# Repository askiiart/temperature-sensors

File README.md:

# Temperature Sensors

An nRF52840-based Zigbee temperature sensor for use with ESPHome, designed for efficiency

## Bill of Materials

|Name                        |Quantity needed|MOQ|Price |Quantity to order|Link                                                                                           |Total    |
|----------------------------|---------------|---|------|-----------------|-----------------------------------------------------------------------------------------------|---------|
|2450AT43F0100001E           |1              |1  |1.1034|1                |https://www.lcsc.com/product-detail/C17192881.html                                             |1.1034   |
|32.768k crystal             |1              |5  |0.2553|5                |https://www.lcsc.com/product-detail/C46257428.html                                             |1.2765   |
|32M crystal                 |1              |10 |0.0564|10               |https://www.lcsc.com/product-detail/C42464320.html                                             |0.564    |
|1pF cap                     |1              |100|0.0085|100              |https://www.lcsc.com/product-detail/C5137611.html                                              |0.85     |
|1.2pF cap                   |1              |100|0.0038|100              |https://www.lcsc.com/product-detail/C1638.html                                                 |0.38     |
|20pF cap                    |2              |100|0.0089|100              |https://www.lcsc.com/product-detail/C5137583.html                                              |0.89     |
|10uF cap                    |3              |50 |0.083 |50               |https://www.lcsc.com/product-detail/C1691.html                                                 |4.15     |
|1uF cap                     |1              |50 |0.0217|50               |https://www.lcsc.com/product-detail/C29936.html                                                |1.085    |
|100pF cap                   |2              |50 |0.0174|50               |https://www.lcsc.com/product-detail/C576846.html                                               |0.87     |
|47nF cap                    |1              |100|0.0077|100              |https://www.lcsc.com/product-detail/C576852.html                                               |0.77     |
|100nF cap                   |5              |50 |0.0179|50               |https://www.lcsc.com/product-detail/C5137636.html                                              |0.895    |
|100uF cap                   |1              |5  |0.3214|5                |https://www.lcsc.com/product-detail/C521072.html                                               |1.607    |
|1nF cap                     |1              |100|0.0049|100              |https://www.lcsc.com/product-detail/C17702741.html                                             |0.49     |
|10pF can                    |1              |100|0.0059|100              |https://www.lcsc.com/product-detail/C1634.html                                                 |0.59     |
|Green LED                   |1              |1  |0.29  |1                |https://www.digikey.com/en/products/detail/sunled/XZVG53W-8/4745971                            |0.29     |
|Red LED                     |1              |1  |0.27  |1                |https://www.digikey.com/en/products/detail/sunled/XZMDK53W-8/4745952                           |0.27     |
|Diodes                      |4              |50 |0.0112|50               |https://www.lcsc.com/product-detail/C191023.html                                               |0.56     |
|JST S3B-PH-SM4-TB           |2              |1  |0.57  |2                |https://www.digikey.com/en/products/detail/jst-sales-america-inc/S3B-PH-SM4-TB/926656          |1.14     |
|JST S2B-PH-SM4-TB           |1              |5  |0.2055|5                |https://www.lcsc.com/product-detail/C295747.html                                               |1.0275   |
|4.7nH inductor              |1              |5  |0.0863|5                |https://www.lcsc.com/product-detail/C2043858.html                                              |0.4315   |
|2.2nH inductor              |1              |10 |0.0785|10               |https://www.lcsc.com/product-detail/C412264.html                                               |0.785    |
|10uH inductor               |1              |10 |0.0564|10               |https://www.lcsc.com/product-detail/C76798.html                                                |0.564    |
|15nH inductor               |1              |20 |0.0666|20               |https://www.lcsc.com/product-detail/C98055.html                                                |1.332    |
|AO3401A (PMOS)              |3              |20 |0.0371|20               |https://www.lcsc.com/product-detail/C347476.html                                               |0.742    |
|1M resistor                 |3              |100|0.0037|100              |https://www.lcsc.com/product-detail/C2907003.html                                              |0.37     |
|10k resistor                |2              |100|0.0057|100              |https://www.lcsc.com/product-detail/C844918.html                                               |0.57     |
|5.1k resistor               |2              |100|0.0028|100              |https://www.lcsc.com/product-detail/C2907044.html                                              |0.28     |
|100k resistor               |1              |100|0.0025|100              |https://www.lcsc.com/product-detail/C2907088.html                                              |0.25     |
|300 resistor                |2              |100|0.0029|100              |https://www.lcsc.com/product-detail/C2930092.html                                              |0.29     |
|560k resistor               |1              |100|0.0025|100              |https://www.lcsc.com/product-detail/C23203.html                                                |0.25     |
|180k resistor               |1              |100|0.0027|100              |https://www.lcsc.com/product-detail/C2906999.html                                              |0.27     |
|TS-1088-AR02016 (pushbutton)|1              |10 |0.0557|10               |https://www.lcsc.com/product-detail/C720477.html                                               |0.557    |
|CHS-01B1 (slide switch)     |1              |1  |0.7583|1                |https://www.lcsc.com/product-detail/C3312309.html                                              |0.7583   |
|NTC themistor               |1              |10 |0.0597|10               |https://www.lcsc.com/product-detail/C3152998.html                                              |0.597    |
|nRF52840-QFAA-F-R7          |1              |1  |6.54  |1                |https://www.digikey.com/en/products/detail/nordic-semiconductor-asa/NRF52840-QFAA-F-R7/15929801|6.54     |
|TP4057                      |1              |10 |0.0413|10               |https://www.lcsc.com/product-detail/C725791.html                                               |0.413    |
|TPS63051RMWR                |1              |1  |1.022 |1                |https://www.lcsc.com/product-detail/C139412.html                                               |1.022    |
|SN74LVC1G00DCKR (inverter)  |1              |10 |0.0299|10               |https://www.lcsc.com/product-detail/C19829626.html                                             |0.299    |
|                            |               |   |      |                 |                                                                                               |         |
|PCB                         |1              |1  |2     |1                |https://cart.jlcpcb.com/quote                                                                  |2        |
|                            |               |   |      |                 |                                                                                               |         |
|JLCPCB shipping             |               |   |      |                 |                                                                                               |3.12     |
|LCSC shipping               |               |   |      |                 |                                                                                               |10.76    |
|Digikey shipping            |               |   |      |                 |                                                                                               |$4.99    |
|                            |               |   |      |                 |                                                                                               |         |
|Subtotal                    |               |   |      |                 |                                                                                               |55.9992  |
|Total                       |               |   |      |                 |                                                                                               |60.619134|

## Production notes

The layer stackup should be JLC0616H-3313.

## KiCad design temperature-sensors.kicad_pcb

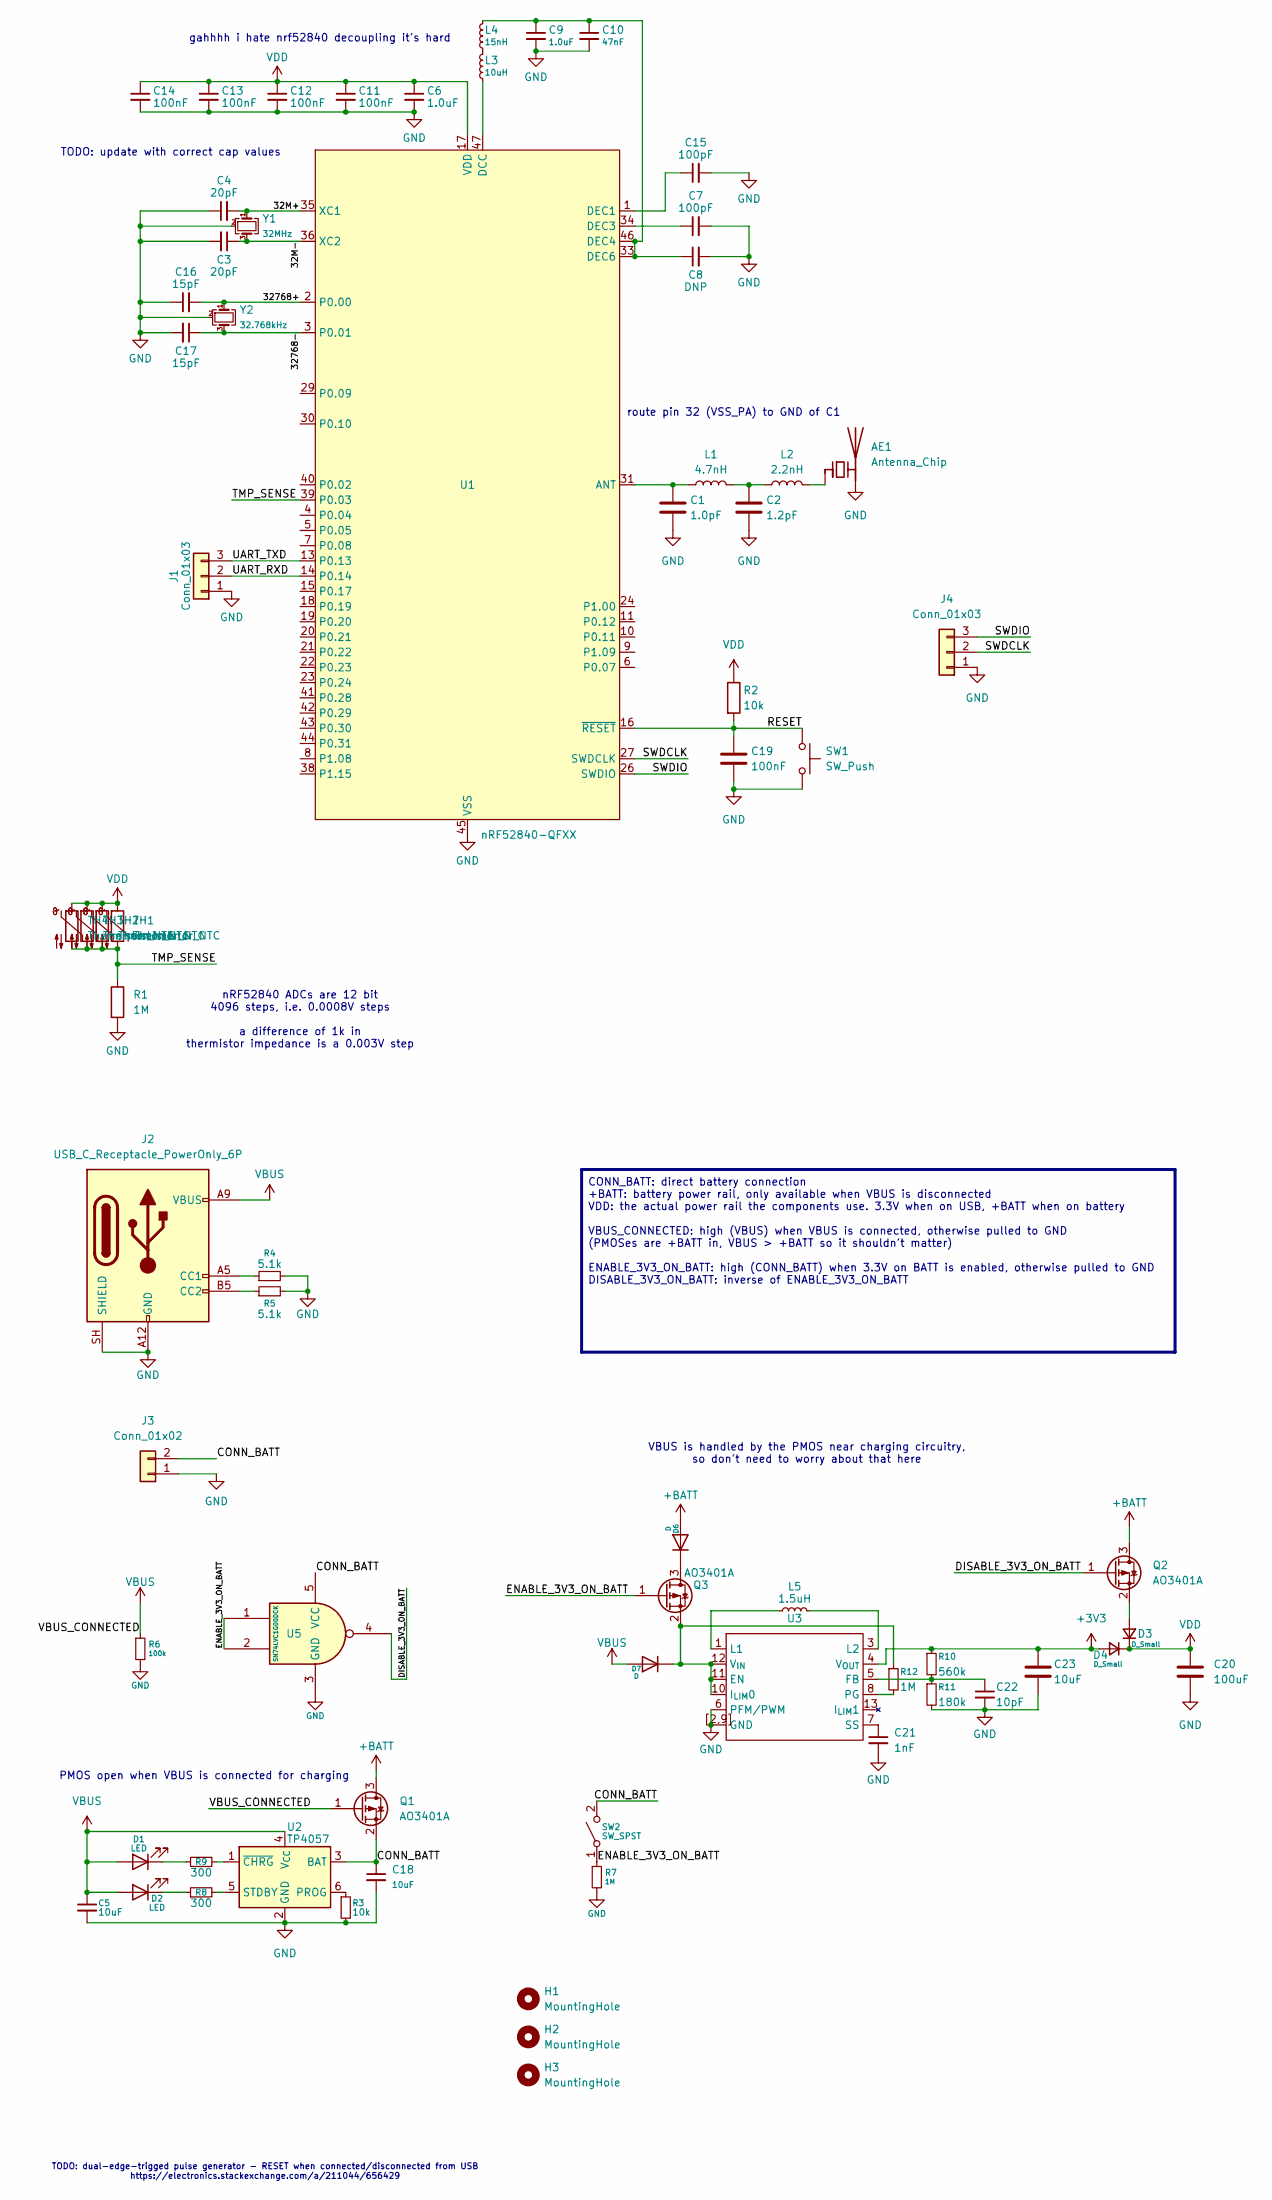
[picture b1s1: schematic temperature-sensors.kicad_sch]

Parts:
AE1: Antenna_Chip; Johanson_2450AT43F0100
C1: 1.0pF; C_0603_1608Metric
C2: 1.2pF; C_0603_1608Metric
C3, C4: 20pF; C_0603_1608Metric
C5, C18, C23: 10uF; C_0603_1608Metric
C6, C9: 1.0uF; C_0603_1608Metric
C7, C15: 100pF; C_0603_1608Metric
C8: DNP; C_0603_1608Metric
C10: 47nF; C_0603_1608Metric
C11, C12, C13, C14, C19: 100nF; C_0603_1608Metric
C16, C17: 15pF; C_0603_1608Metric
C20: 100uF; C_0805_2012Metric
C21: 1nF; C_0603_1608Metric
C22: 10pF; C_0603_1608Metric
D1, D2: LED; D_0603_1608Metric
D3, D4: D_Small; D_SOD-323
D6, D7: D; D_SOD-323
H1, H2, H3: MountingHole; MountingHole_2.2mm_M2_ISO7380
J1, J4: Conn_01x03; JST_PH_S3B-PH-SM4-TB_1x03-1MP_P2.00mm_Horizontal
J2: USB_C_Receptacle_PowerOnly_6P; USB_C_Receptacle_GCT_USB4135-GF-A_6P_TopMnt_Horizontal
J3: Conn_01x02; JST_PH_S2B-PH-SM4-TB_1x02-1MP_P2.00mm_Horizontal
L1: 4.7nH; L_0402_1005Metric
L2: 2.2nH; L_0402_1005Metric
L3: 10uH; L_0603_1608Metric
L4: 15nH; L_0402_1005Metric
L5: 1.5uH; L_1008_2520Metric
Q1, Q2, Q3: AO3401A; SOT-23
R1, R7, R12: 1M; R_0603_1608Metric
R2, R3: 10k; R_0603_1608Metric
R4, R5: 5.1k; R_0603_1608Metric
R6: 100k; R_0603_1608Metric
R8, R9: 300; R_0603_1608Metric
R10: 560k; R_0603_1608Metric
R11: 180k; R_0603_1608Metric
SW1: SW_Push; SW_SPST_TS-1088-xR020
SW2: SW_SPST; SW_DIP_SPSTx01_Slide_Copal_CHS-01B_W7.62mm_P1.27mm
TH1: Thermistor_NTC; R_0201_0603Metric
TH2: Thermistor_NTC; R_0402_1005Metric
TH3: Thermistor_NTC; R_0603_1608Metric
TH4: Thermistor_NTC; R_0805_2012Metric
U1: nRF52840-QFXX; QFN-48-1EP_6x6mm_P0.4mm_EP4.6x4.6mm_ThermalVias
U2: TP4057; TSOT-23-6
U3: TPS63051-QFN-12-HotRod
U5: SN74LVC1G00DCK; Texas_R-PDSO-G5_DCK-5
Y1: 32MHz; Crystal_SMD_3225-4Pin_3.2x2.5mm
Y2: 32.768kHz; Crystal_SMD_3225-4Pin_3.2x2.5mm

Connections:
+3V3: C23.1, D4.2 (A), R10.1, U3.4 (V_{OUT})
+BATT: D6.2 (A), Q1.3 (D), Q2.3 (D)
/32M+: C4.2, U1.35 (XC1), Y1.1
/32M-: C3.1, U1.36 (XC2), Y1.3
/32768+: C16.2, U1.2 (P0.00), Y2.1
/32768-: C17.1, U1.3 (P0.01), Y2.3
/CONN_BATT: C18.1, J3.2, Q1.2 (S), SW2.2 (B), U2.3 (BAT), U5.5 (VCC)
/DISABLE_3V3_ON_BATT: Q2.1 (G), U5.4
/ENABLE_3V3_ON_BATT: Q3.1 (G), R7.1, SW2.1 (A), U5.1, U5.2
/RESET: C19.1, R2.2, SW1.1, U1.16 (~RESET)
/SWDCLK: J4.2, U1.27 (SWDCLK)
/SWDIO: J4.3, U1.26 (SWDIO)
/TMP_SENSE: R1.1, TH1.2, TH2.2, TH3.2, TH4.2, U1.39 (P0.03)
/UART_RXD: J1.2, U1.14 (P0.14)
/UART_TXD: J1.3, U1.13 (P0.13)
GND: AE1.2 (PCB_Trace), C1.2, C2.2, C3.2, C4.1, C5.2, C6.2, C7.2, C8.2, C9.2, C10.2, C11.2, C12.2, C13.2, C14.2, C15.2, C16.1, C17.2, C18.2, C19.2, C20.2, C21.2, C22.2, C23.2, J1.1, J2.A12 (GND), J2.B12 (GND), J2.SH (SHIELD), J3.1, J4.1, R1.2, R3.2, R4.2, R5.2, R6.2, R7.2, R11.2, SW1.2, U1.32 (VSS_PA), U1.45 (VSS), U1.49 (VSS), U2.2 (GND), U3.2 (GND), U3.6 (PFM/PWM), U3.9 (GND), U3.[2,9] (GND), U5.3 (GND), Y1.2 (G), Y1.4 (G), Y2.2 (G), Y2.4 (G)
unnamed: AE1.1 (FEED), L2.2
unnamed: C2.1, L1.2, L2.1
unnamed: D1.1 (K), R9.1
unnamed: D2.1 (K), R8.1
unnamed: D3.2 (A), Q2.2 (S)
unnamed: D6.1 (K), Q3.3 (D)
unnamed: D7.1 (K), Q3.2 (S), R12.1, U3.10 (I_{LIM}0), U3.11 (EN), U3.12 (V_{IN})
unnamed: J2.A5 (CC1), R4.1
unnamed: J2.B5 (CC2), R5.1
unnamed: L3.2, L4.1
unnamed: C1.1, L1.1, U1.31 (ANT)
unnamed: L3.1, U1.47 (DCC)
unnamed: C15.1, U1.1 (DEC1)
unnamed: C7.1, U1.34 (DEC3)
unnamed: C8.1, C9.1, C10.1, L4.2, U1.33 (DEC6), U1.46 (DEC4)
unnamed: R3.1, U2.6 (PROG)
unnamed: R8.2, U2.5 (STDBY)
unnamed: R9.2, U2.1 (~CHRG)
unnamed: C22.1, R10.2, R11.1, U3.5 (FB)
unnamed: L5.1, U3.1 (L1)
unnamed: L5.2, U3.3 (L2)
unnamed: R12.2, U3.8 (PG)
unnamed: C21.1, U3.7 (SS)
VBUS: C5.1, D1.2 (A), D2.2 (A), D7.2 (A), J2.A9 (VBUS), J2.B9 (VBUS), Q1.1 (G), R6.1, U2.4 (V_{CC})
VDD: C6.1, C11.1, C12.1, C13.1, C14.1, C20.1, D3.1 (K), D4.1 (K), R2.1, TH1.1, TH2.1, TH3.1, TH4.1, U1.12 (VDD), U1.17 (VDD), U1.25 (VDD), U1.37 (VDD), U1.48 (VDD)

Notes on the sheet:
gahhhh i hate nrf52840 decoupling it's hard
VBUS is handled by the PMOS near charging circuitry, so don't need to worry about that here
TODO: update with correct cap values
route pin 32 (VSS_PA) to GND of C1
nRF52840 ADCs are 12 bit 4096 steps, i.e. 0.0008V steps a difference of 1k in thermistor impedance is a 0.003V step
CONN_BATT: direct battery connection +BATT: battery power rail, only available when VBUS is disconnected VDD: the actual power rail the components use. 3.3V when on USB, +BATT when on battery VBUS_CONNECTED: high (VBUS) when VBUS is connected, otherwise pulled to GND (PMOSes are +BATT in, VBUS > +B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
TODO: dual-edge-trigged pulse generator - RESET when connected/disconnected from USB https://electronics.stackexchange.com/a/211044/656429
PMOS open when VBUS is connected for charging

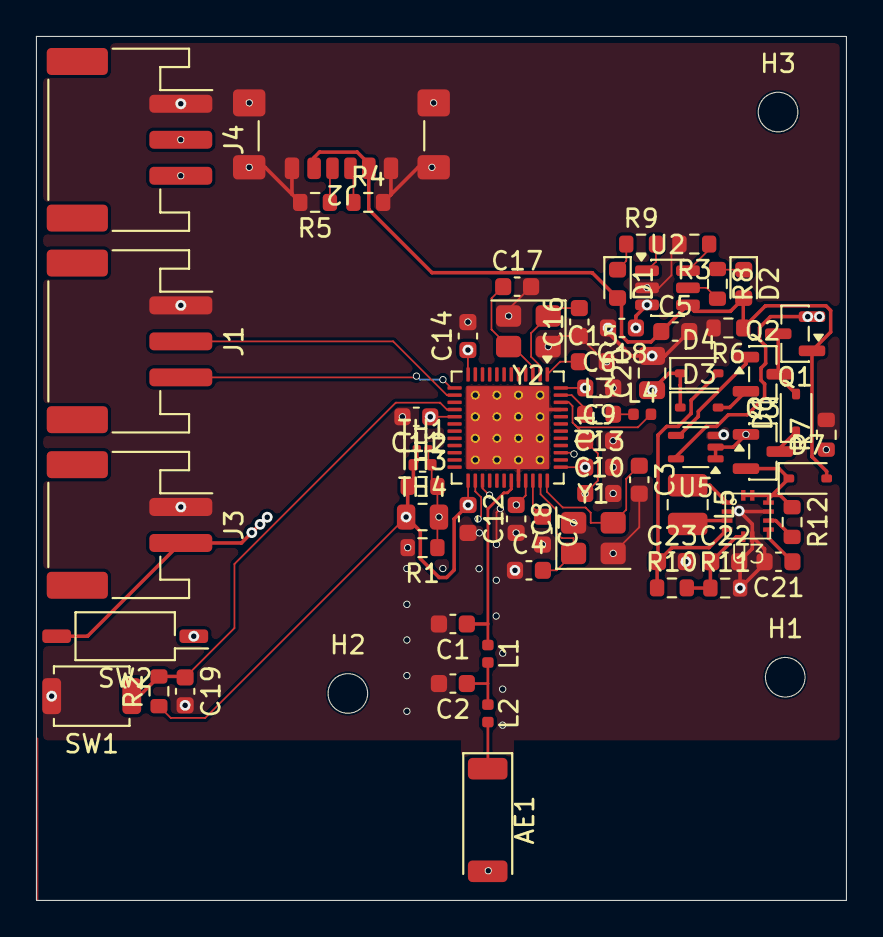
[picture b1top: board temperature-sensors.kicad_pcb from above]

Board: 6 copper layers, 45.0 x 48.0 mm, 69 parts (0 on the bottom side), 41 nets.

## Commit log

2026-06-21 add actually decent power circuitry - can charge and power itself off USB simultaneously
2026-06-21 get rid of extra PMOS
2026-06-22 add a bunch of stuff idk i'm just committing
2026-06-28 finished schematic idk
2026-06-29 aaaaaa
2026-06-30 the pcb is pcb'd idkkkk
2026-06-30 add BOM and images and yeag
